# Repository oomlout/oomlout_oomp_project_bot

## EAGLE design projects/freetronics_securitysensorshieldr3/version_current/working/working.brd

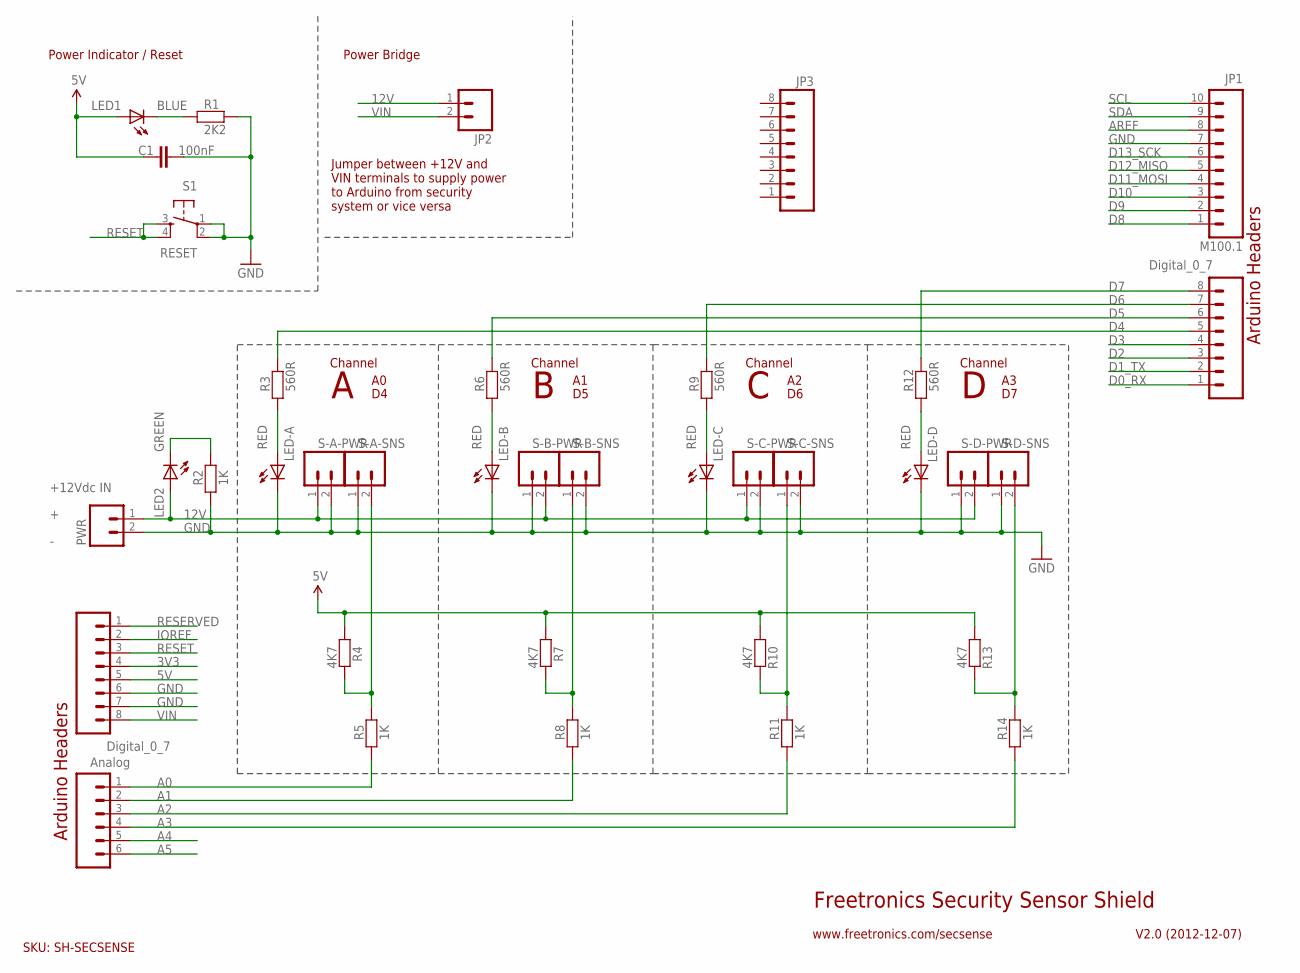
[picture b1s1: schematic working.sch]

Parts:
C1: 100nF; FREETRONICS_CAP-PTH-SMALL
J1, J3: Digital_0_7; 1X08
J2: Analog; 1X06
JP1: M100.1; 1X10
JP2: M02PTH; 1X02
JP3: M08; TERMINALBLOCK_3.5MM_8
LED1: BLUE; LED3MM
LED2: GREEN; LED3MM
LED-A: RED; LED3MM
LED-B: RED; LED3MM
LED-C: RED; LED3MM
LED-D: RED; LED3MM
PWR: M025MM; SCREWTERMINAL-5MM-2
R1: 2K2; FREETRONICS_AXIAL-0.4
R2, R5, R8, R11, R14: 1K; FREETRONICS_AXIAL-0.4
R3, R6, R9, R12: 560R; FREETRONICS_AXIAL-0.4
R4, R7, R10, R13: 4K7; FREETRONICS_AXIAL-0.4
S1: RESET; FREETRONICS_TACTILE-PTH
S-A-PWR: M025MM; SCREWTERMINAL-5MM-2
S-A-SNS: M025MM; SCREWTERMINAL-5MM-2
S-B-PWR: M025MM; SCREWTERMINAL-5MM-2
S-B-SNS: M025MM; SCREWTERMINAL-5MM-2
S-C-PWR: M025MM; SCREWTERMINAL-5MM-2
S-C-SNS: M025MM; SCREWTERMINAL-5MM-2
S-D-PWR: M025MM; SCREWTERMINAL-5MM-2
S-D-SNS: M025MM; SCREWTERMINAL-5MM-2

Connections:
3V3: J3.4
5V: C1.1, J3.5, LED1.A, R4.P$1 (1), R7.P$1 (1), R10.P$1 (1), R13.P$1 (1)
12V: JP2.1, LED2.A, PWR.1, S-A-PWR.1, S-B-PWR.2, S-C-PWR.1, S-D-PWR.2
A0: J2.1, R5.P$1 (1)
A1: J2.2, R8.P$1 (1)
A2: J2.3, R11.P$1 (1)
A3: J2.4, R14.P$1 (1)
A4: J2.5
A5: J2.6
AREF: JP1.8
D0_RX: J1.1
D1_TX: J1.2
D2: J1.3
D3: J1.4
D4: J1.5, R3.P$2 (2)
D5: J1.6, R6.P$2 (2)
D6: J1.7, R9.P$2 (2)
D7: J1.8, R12.P$2 (2)
D8: JP1.1
D9: JP1.2
D10: JP1.3
D11_MOSI: JP1.4
D12_MISO: JP1.5
D13_SCK: JP1.6
GND: C1.2, J3.6, J3.7, JP1.7, LED-A.K (C), LED-B.K (C), LED-C.K (C), LED-D.K (C), PWR.2, R1.P$2 (2), R2.P$1 (1), S1.1, S1.2, S-A-PWR.2, S-A-SNS.1, S-B-PWR.1, S-B-SNS.2, S-C-PWR.2, S-C-SNS.2, S-D-PWR.1, S-D-SNS.1
IOREF: J3.2
unnamed: LED2.K (C), R2.P$2 (2)
unnamed: R7.P$2 (2), R8.P$2 (2), S-B-SNS.1
unnamed: LED1.K (C), R1.P$1 (1)
unnamed: R10.P$2 (2), R11.P$2 (2), S-C-SNS.1
unnamed: LED-D.A, R12.P$1 (1)
unnamed: LED-C.A, R9.P$1 (1)
unnamed: LED-B.A, R6.P$1 (1)
unnamed: LED-A.A, R3.P$1 (1)
unnamed: R13.P$2 (2), R14.P$2 (2), S-D-SNS.2
unnamed: R4.P$2 (2), R5.P$2 (2), S-A-SNS.2
RESERVED: J3.1
RESET: J3.3, S1.3, S1.4
SCL: JP1.10
SDA: JP1.9
VIN: J3.8, JP2.2

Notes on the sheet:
Freetronics Security Sensor Shield
V2.0 (2012-12-07)
SKU: SH-SECSENSE
Power Indicator / Reset
Arduino Headers
www.freetronics.com/secsense
Channel
Power Bridge
Jumper between +12V and VIN terminals to supply power to Arduino from security system or vice versa
+12Vdc IN

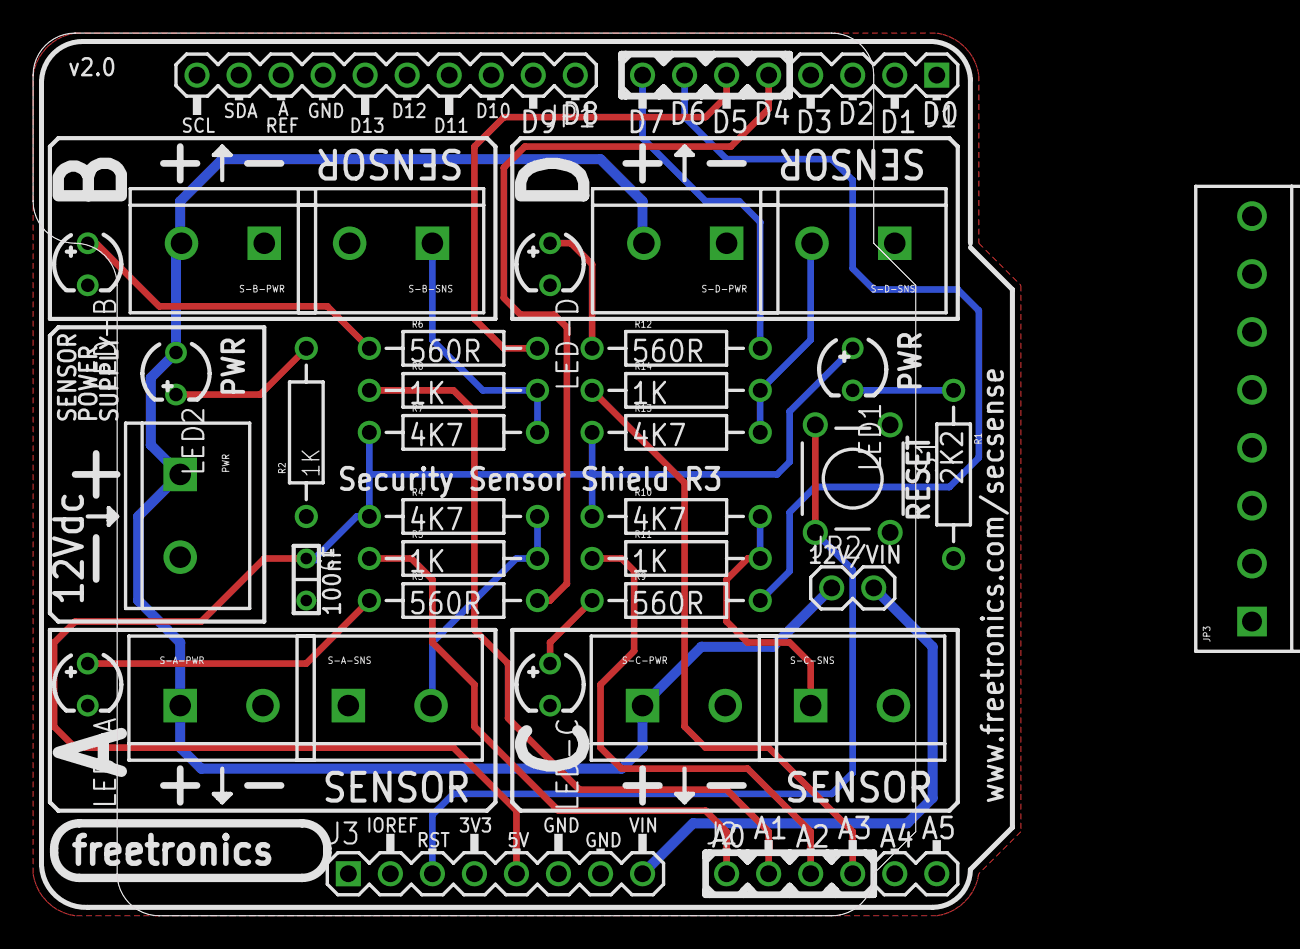
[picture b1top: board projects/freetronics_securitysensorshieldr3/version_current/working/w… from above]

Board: 2 copper layers, 53.3 x 53.3 mm, 37 parts (0 on the bottom side), 23 nets.

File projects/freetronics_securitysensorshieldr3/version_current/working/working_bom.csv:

"Id";"Designator";"Footprint";"Quantity";"Designation";"Supplier and ref";
1;"S-A-SNS0,S-D-PWR0,PWR0,S-B-SNS0,S-D-SNS0,S-C-SNS0,S-A-PWR0,S-C-PWR0,S-B-PWR0";"SCREWTERMINAL-5MM-2";9;"";;;
2;"R9,R3,R6,R12";"FREETRONICS_AXIAL-0.4";4;"560R";;;
3;"R14,R11,R5,R2,R8";"FREETRONICS_AXIAL-0.4";5;"1K";;;
4;"S1";"FREETRONICS_TACTILE-PTH";1;"RESET";;;
5;"LED-B0,LED-C0,LED-A0,LED-D0";"LED3MM";4;"RED";;;
6;"J1,J3";"1X08";2;"Digital_0_7";;;
7;"J2";"1X06";1;"Analog";;;
8;"R13,R7,R4,R10";"FREETRONICS_AXIAL-0.4";4;"4K7";;;
9;"LED1";"LED3MM";1;"BLUE";;;
10;"JP3";"TERMINALBLOCK_3.5MM_8";1;"";;;
11;"R1";"FREETRONICS_AXIAL-0.4";1;"2K2";;;
12;"JP1";"1X10";1;"M100.1";;;
13;"LED2";"LED3MM";1;"GREEN";;;
14;"C1";"FREETRONICS_CAP-PTH-SMALL";1;"100nF";;;
15;"JP2";"1X02";1;"";;;

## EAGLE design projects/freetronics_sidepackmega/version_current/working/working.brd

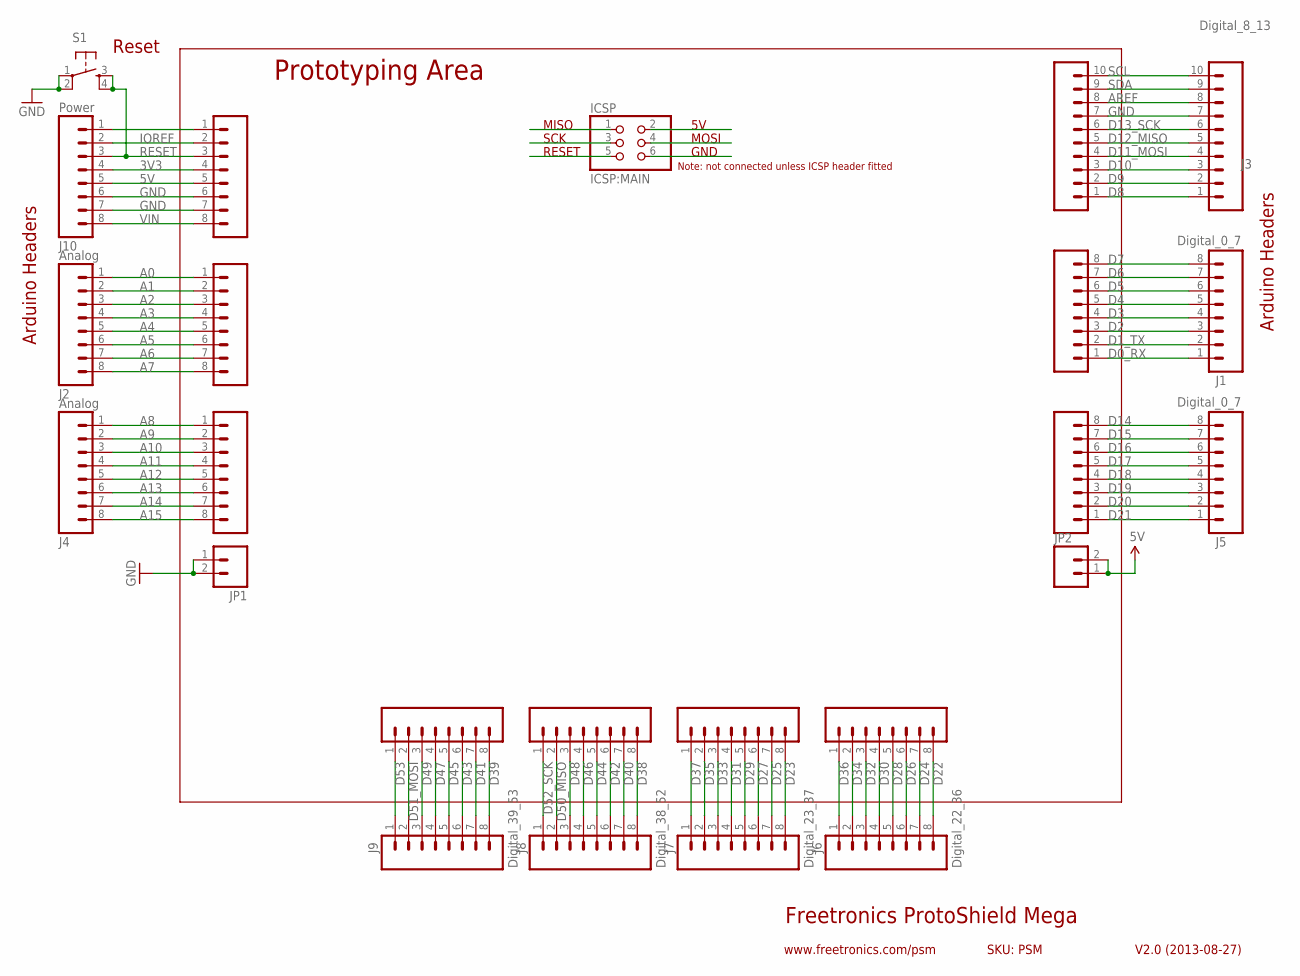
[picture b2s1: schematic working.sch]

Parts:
ICSP: ICSP:MAIN; 2X03
J1, J5: Digital_0_7; 1X08
J2, J4: Analog; 1X08
J3: Digital_8_13; 1X10
J6: Digital_22_36; 1X08
J7: Digital_23_37; 1X08
J8: Digital_38_52; 1X08
J9: Digital_39_53; 1X08
J10: Power; 1X08
JP1, JP2: M02PTH; 1X02
S1: TAC_SWITCHPTH; TACTILE-PTH
SL1, SL5, SL6, SL7, SL8, SL9: Digital_0_7; 1X08
SL2, SL4: Analog; 1X08
SL3: Digital_8_13; 1X10
SLP: Power; 1X08

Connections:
3V3: J10.4, SLP.4
5V: J10.5, JP2.1, JP2.2, SLP.5
A0: J2.1, SL2.1
A1: J2.2, SL2.2
A2: J2.3, SL2.3
A3: J2.4, SL2.4
A4: J2.5, SL2.5
A5: J2.6, SL2.6
A6: J2.7, SL2.7
A7: J2.8, SL2.8
A8: J4.1, SL4.1
A9: J4.2, SL4.2
A10: J4.3, SL4.3
A11: J4.4, SL4.4
A12: J4.5, SL4.5
A13: J4.6, SL4.6
A14: J4.7, SL4.7
A15: J4.8, SL4.8
AREF: J3.8, SL3.8
D0_RX: J1.1, SL1.1
D1_TX: J1.2, SL1.2
D2: J1.3, SL1.3
D3: J1.4, SL1.4
D4: J1.5, SL1.5
D5: J1.6, SL1.6
D6: J1.7, SL1.7
D7: J1.8, SL1.8
D8: J3.1, SL3.1
D9: J3.2, SL3.2
D10: J3.3, SL3.3
D11_MOSI: J3.4, SL3.4
D12_MISO: J3.5, SL3.5
D13_SCK: J3.6, SL3.6
D14: J5.8, SL5.8
D15: J5.7, SL5.7
D16: J5.6, SL5.6
D17: J5.5, SL5.5
D18: J5.4, SL5.4
D19: J5.3, SL5.3
D20: J5.2, SL5.2
D21: J5.1, SL5.1
D22: J6.8, SL6.8
D23: J7.8, SL7.8
D24: J6.7, SL6.7
D25: J7.7, SL7.7
D26: J6.6, SL6.6
D27: J7.6, SL7.6
D28: J6.5, SL6.5
D29: J7.5, SL7.5
D30: J6.4, SL6.4
D31: J7.4, SL7.4
D32: J6.3, SL6.3
D33: J7.3, SL7.3
D34: J6.2, SL6.2
D35: J7.2, SL7.2
D36: J6.1, SL6.1
D37: J7.1, SL7.1
D38: J8.8, SL8.8
D39: J9.8, SL9.8
D40: J8.7, SL8.7
D41: J9.7, SL9.7
D42: J8.6, SL8.6
D43: J9.6, SL9.6
D44: J8.5, SL8.5
D45: J9.5, SL9.5
D46: J8.4, SL8.4
D47: J9.4, SL9.4
D48: J8.3, SL8.3
D49: J9.3, SL9.3
D50_MISO: J8.2, SL8.2
D51_MOSI: J9.2, SL9.2
D52_SCK: J8.1, SL8.1
D53: J9.1, SL9.1
GND: J3.7, J10.6, J10.7, JP1.1, JP1.2, S1.1, S1.2, SL3.7, SLP.6, SLP.7
IOREF: J10.2, SLP.2
unnamed: J10.1, SLP.1
RESET: J10.3, S1.3, S1.4, SLP.3
SCL: J3.10, SL3.10
SDA: J3.9, SL3.9
VIN: J10.8, SLP.8

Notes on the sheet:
Freetronics ProtoShield Mega
V2.0 (2013-08-27)
www.freetronics.com/psm
SKU: PSM
Prototyping Area
Arduino Headers
Reset
GND
MISO
RESET
SCK
MOSI
Note: not connected unless ICSP header fitted

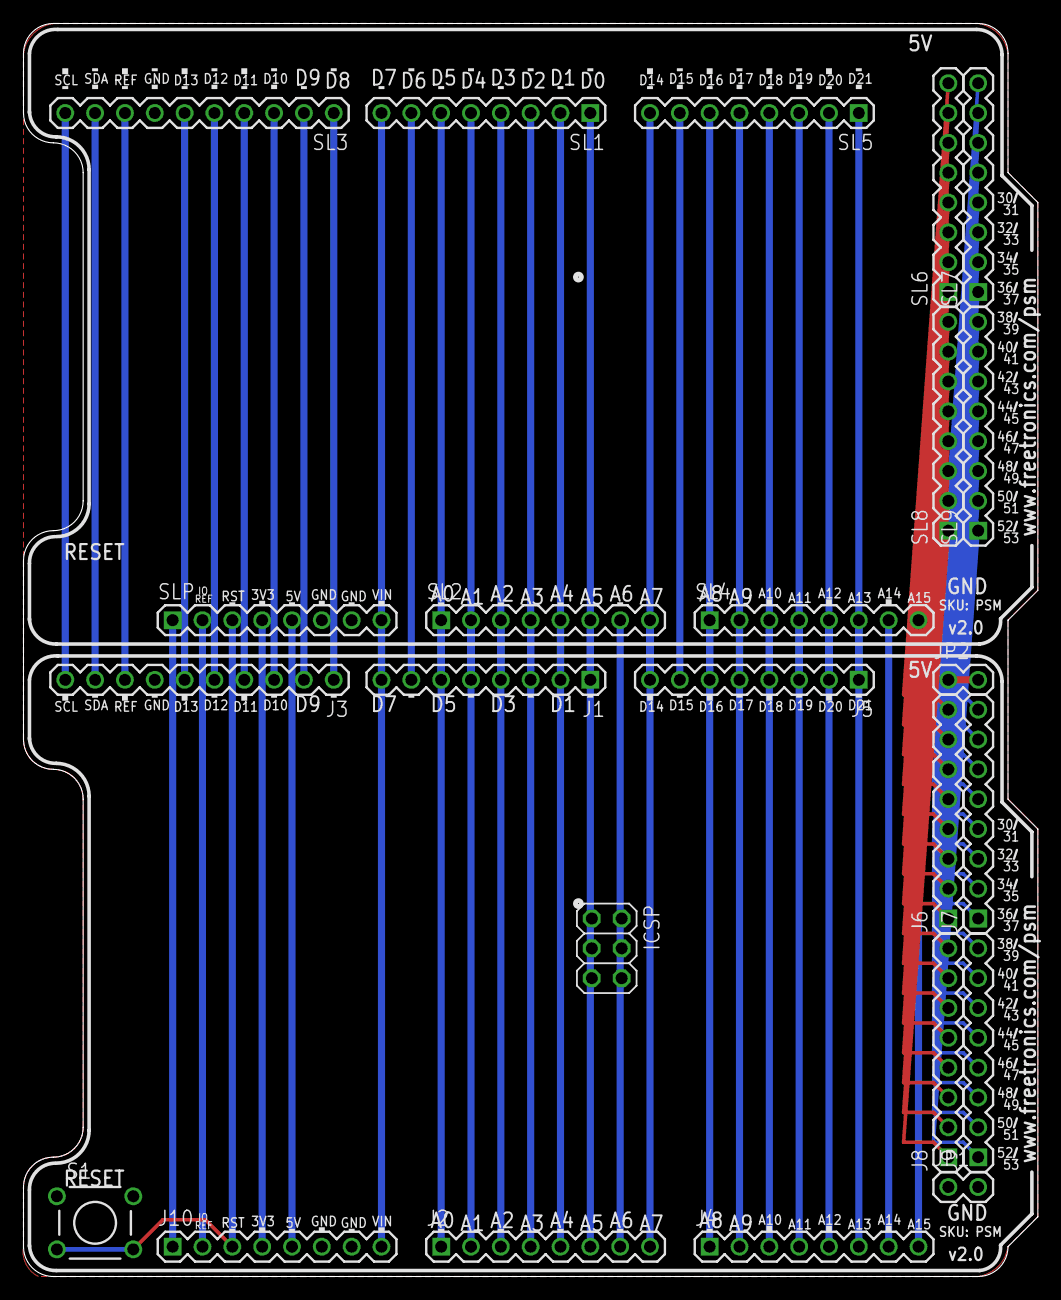
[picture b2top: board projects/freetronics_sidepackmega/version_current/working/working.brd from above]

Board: 2 copper layers, 86.4 x 106.7 mm, 24 parts (0 on the bottom side), 80 nets.

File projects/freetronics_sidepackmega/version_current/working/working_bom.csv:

"Id";"Designator";"Footprint";"Quantity";"Designation";"Supplier and ref";
1;"J1,SL1,J5,SL6,SL9,SL8,SL7,SL5";"1X08";8;"Digital_0_7";;;
2;"J9";"1X08";1;"Digital_39_53";;;
3;"S1";"TACTILE-PTH";1;"";;;
4;"J8";"1X08";1;"Digital_38_52";;;
5;"J7";"1X08";1;"Digital_23_37";;;
6;"ICSP0";"2X03";1;"ICSP:MAIN";;;
7;"JP2,JP1";"1X02";2;"";;;
8;"J6";"1X08";1;"Digital_22_36";;;
9;"SL4,SL2,J2,J4";"1X08";4;"Analog";;;
10;"SLP0,J10";"1X08";2;"Power";;;
11;"SL3,J3";"1X10";2;"Digital_8_13";;;

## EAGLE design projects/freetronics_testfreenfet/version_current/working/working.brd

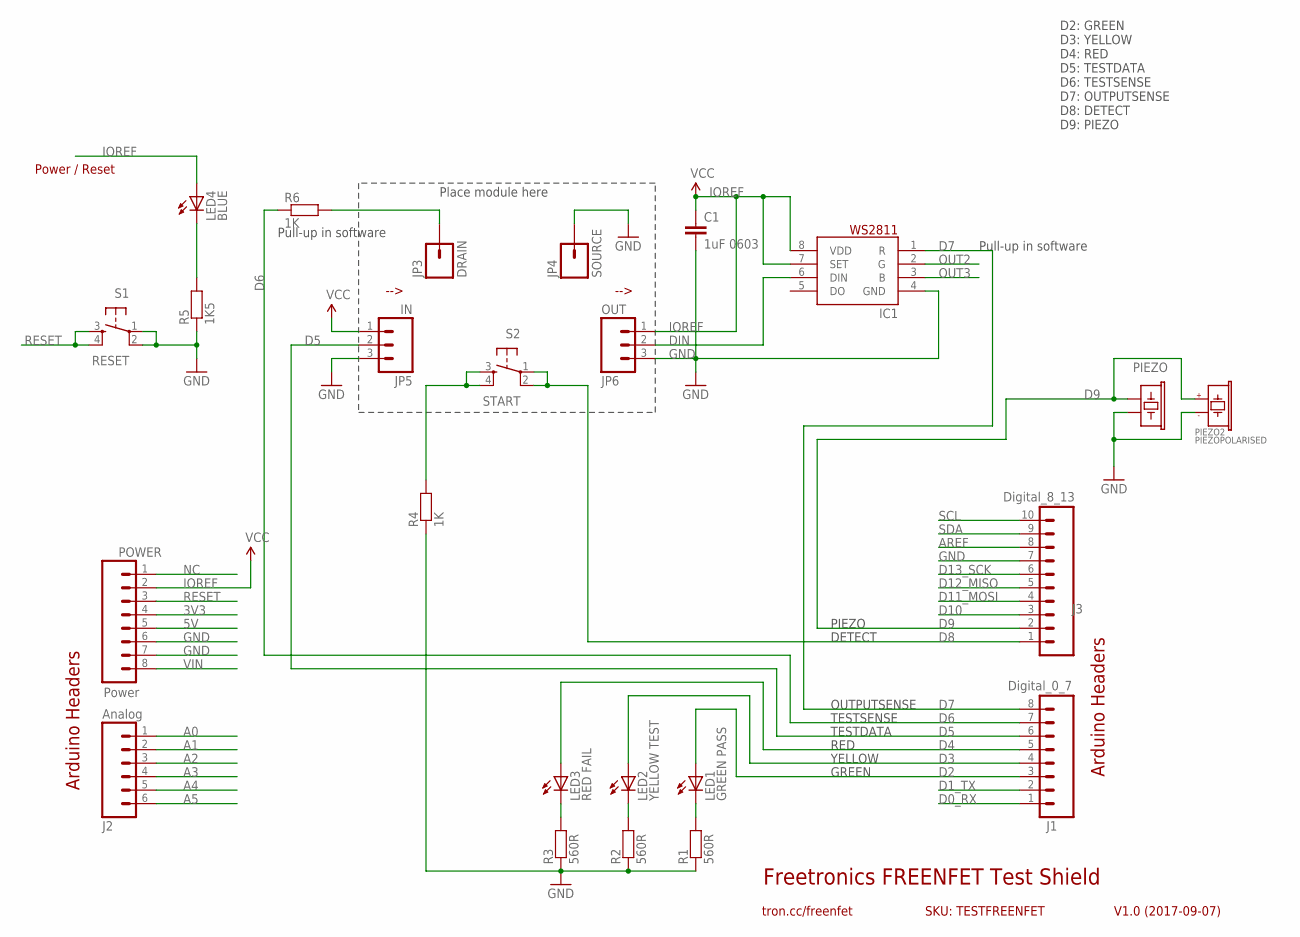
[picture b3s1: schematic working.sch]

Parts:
C1: 1uF 0603; 0603
IC1: WS2811-SOP8; SO08-SKINNYPADS
J1: Digital_0_7; 1X08
J2: Analog; 1X06
J3: Digital_8_13; 1X10
JP3: DRAIN; 1X01_2_1_MM
JP4: SOURCE; 1X01_2_1_MM
JP5: IN; 1X03
JP6: OUT; 1X03
LED1: GREEN PASS; LED-0603
LED2: YELLOW TEST; LED-0603
LED3: RED FAIL; LED-0603
LED4: BLUE; LED-0603
PIEZO: BUZZERSMD12X12; BUZZER-12X12-SMT
PIEZO2: PIEZOPOLARISED; PIEZO12MMWIDEPOLARISED
POWER: Power; 1X08
R1, R2, R3: 560R; 0603
R4, R6: 1K; 0603
R5: 1K5; 0603
S1: RESET; TACTILE-PTH
S2: START; TACTILE-PTH

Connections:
3V3: POWER.4
5V: POWER.5
A0: J2.1
A1: J2.2
A2: J2.3
A3: J2.4
A4: J2.5
A5: J2.6
AREF: J3.8
D0_RX: J1.1
D1_TX: J1.2
D2: J1.3, LED1.A
D3: J1.4, LED2.A
D4: J1.5, LED3.A
D5: J1.6, JP5.2
D6: J1.7, R6.1
D7: IC1.1 (R), J1.8
D8: J3.1, S2.1, S2.2
D9: J3.2, PIEZO.2, PIEZO2.1 (+)
D10: J3.3
D11_MOSI: J3.4
D12_MISO: J3.5
D13_SCK: J3.6
DIN: IC1.6 (DIN), JP6.2
GND: C1.2, IC1.4 (GND), J3.7, JP4.1, JP5.3, JP6.3, PIEZO.1, PIEZO2.2 (-), POWER.6, POWER.7, R1.1, R2.1, R3.1, R4.1, R5.1, S1.1, S1.2
IOREF: C1.1, IC1.7 (SET), IC1.8 (VDD), JP5.1, JP6.1, LED4.A, POWER.2
unnamed: LED1.C, R1.2
unnamed: LED2.C, R2.2
unnamed: LED3.C, R3.2
unnamed: LED4.C, R5.2
unnamed: JP3.1, R6.2
unnamed: R4.2, S2.3, S2.4
NC: POWER.1
OUT2: IC1.2 (G)
OUT3: IC1.3 (B)
RESET: POWER.3, S1.3, S1.4
SCL: J3.10
SDA: J3.9
VIN: POWER.8

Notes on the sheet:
Freetronics FREENFET Test Shield
V1.0 (2017-09-07)
tron.cc/freenfet
SKU: TESTFREENFET
Arduino Headers
Power / Reset
-->
Pull-up in software
Place module here
D2: GREEN D3: YELLOW D4: RED D5: TESTDATA D6: TESTSENSE D7: OUTPUTSENSE D8: DETECT D9: PIEZO
TESTDATA
GREEN
YELLOW
RED
TESTSENSE
OUTPUTSENSE
DETECT
PIEZO

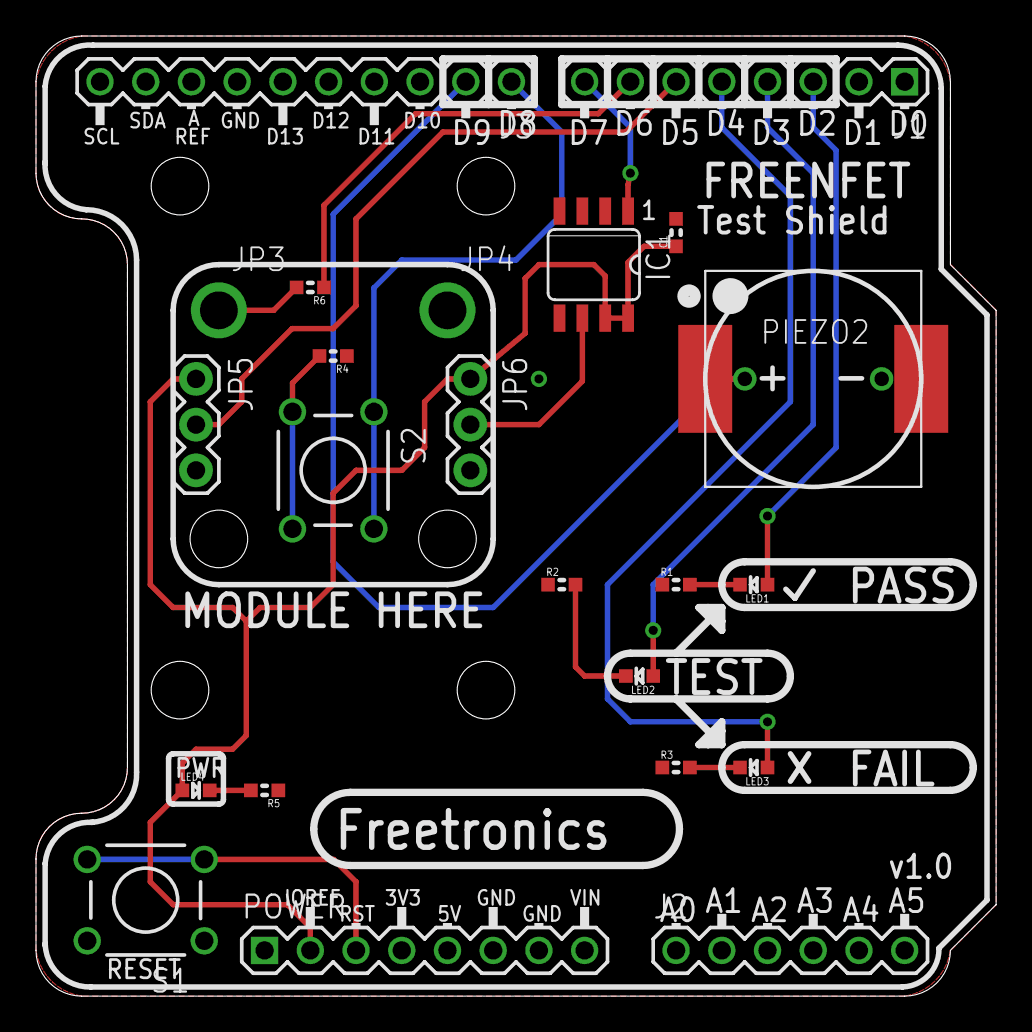
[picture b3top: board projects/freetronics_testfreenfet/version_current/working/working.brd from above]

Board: 2 copper layers, 53.3 x 53.3 mm, 24 parts (0 on the bottom side), 18 nets.

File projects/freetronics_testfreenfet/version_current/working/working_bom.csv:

"Id";"Designator";"Footprint";"Quantity";"Designation";"Supplier and ref";
1;"S2";"TACTILE-PTH";1;"START";;;
2;"JP5";"1X03";1;"IN";;;
3;"C1";"0603";1;"1uF 0603";;;
4;"PIEZO2";"PIEZO12MMWIDEPOLARISED";1;"PIEZOPOLARISED";;;
5;"IC1";"SO08-SKINNYPADS";1;"WS2811-SOP8";;;
6;"LED2";"LED-0603";1;"YELLOW TEST";;;
7;"JP4";"1X01_2_1_MM";1;"SOURCE";;;
8;"R2,R1,R3";"0603";3;"560R";;;
9;"@HOLE2,@HOLE3,@HOLE5,@HOLE1,@HOLE0,@HOLE4";"";6;"";;;
10;"R5";"0603";1;"1K5";;;
11;"POWER0";"1X08";1;"Power";;;
12;"LED3";"LED-0603";1;"RED FAIL";;;
13;"LED4";"LED-0603";1;"BLUE";;;
14;"J2";"1X06";1;"Analog";;;
15;"J1";"1X08";1;"Digital_0_7";;;
16;"J3";"1X10";1;"Digital_8_13";;;
17;"JP6";"1X03";1;"OUT";;;
18;"S1";"TACTILE-PTH";1;"RESET";;;
19;"LED1";"LED-0603";1;"GREEN PASS";;;
20;"R6,R4";"0603";2;"1K";;;
21;"PIEZO0";"BUZZER-12X12-SMT";1;"BUZZERSMD12X12";;;
22;"JP3";"1X01_2_1_MM";1;"DRAIN";;;

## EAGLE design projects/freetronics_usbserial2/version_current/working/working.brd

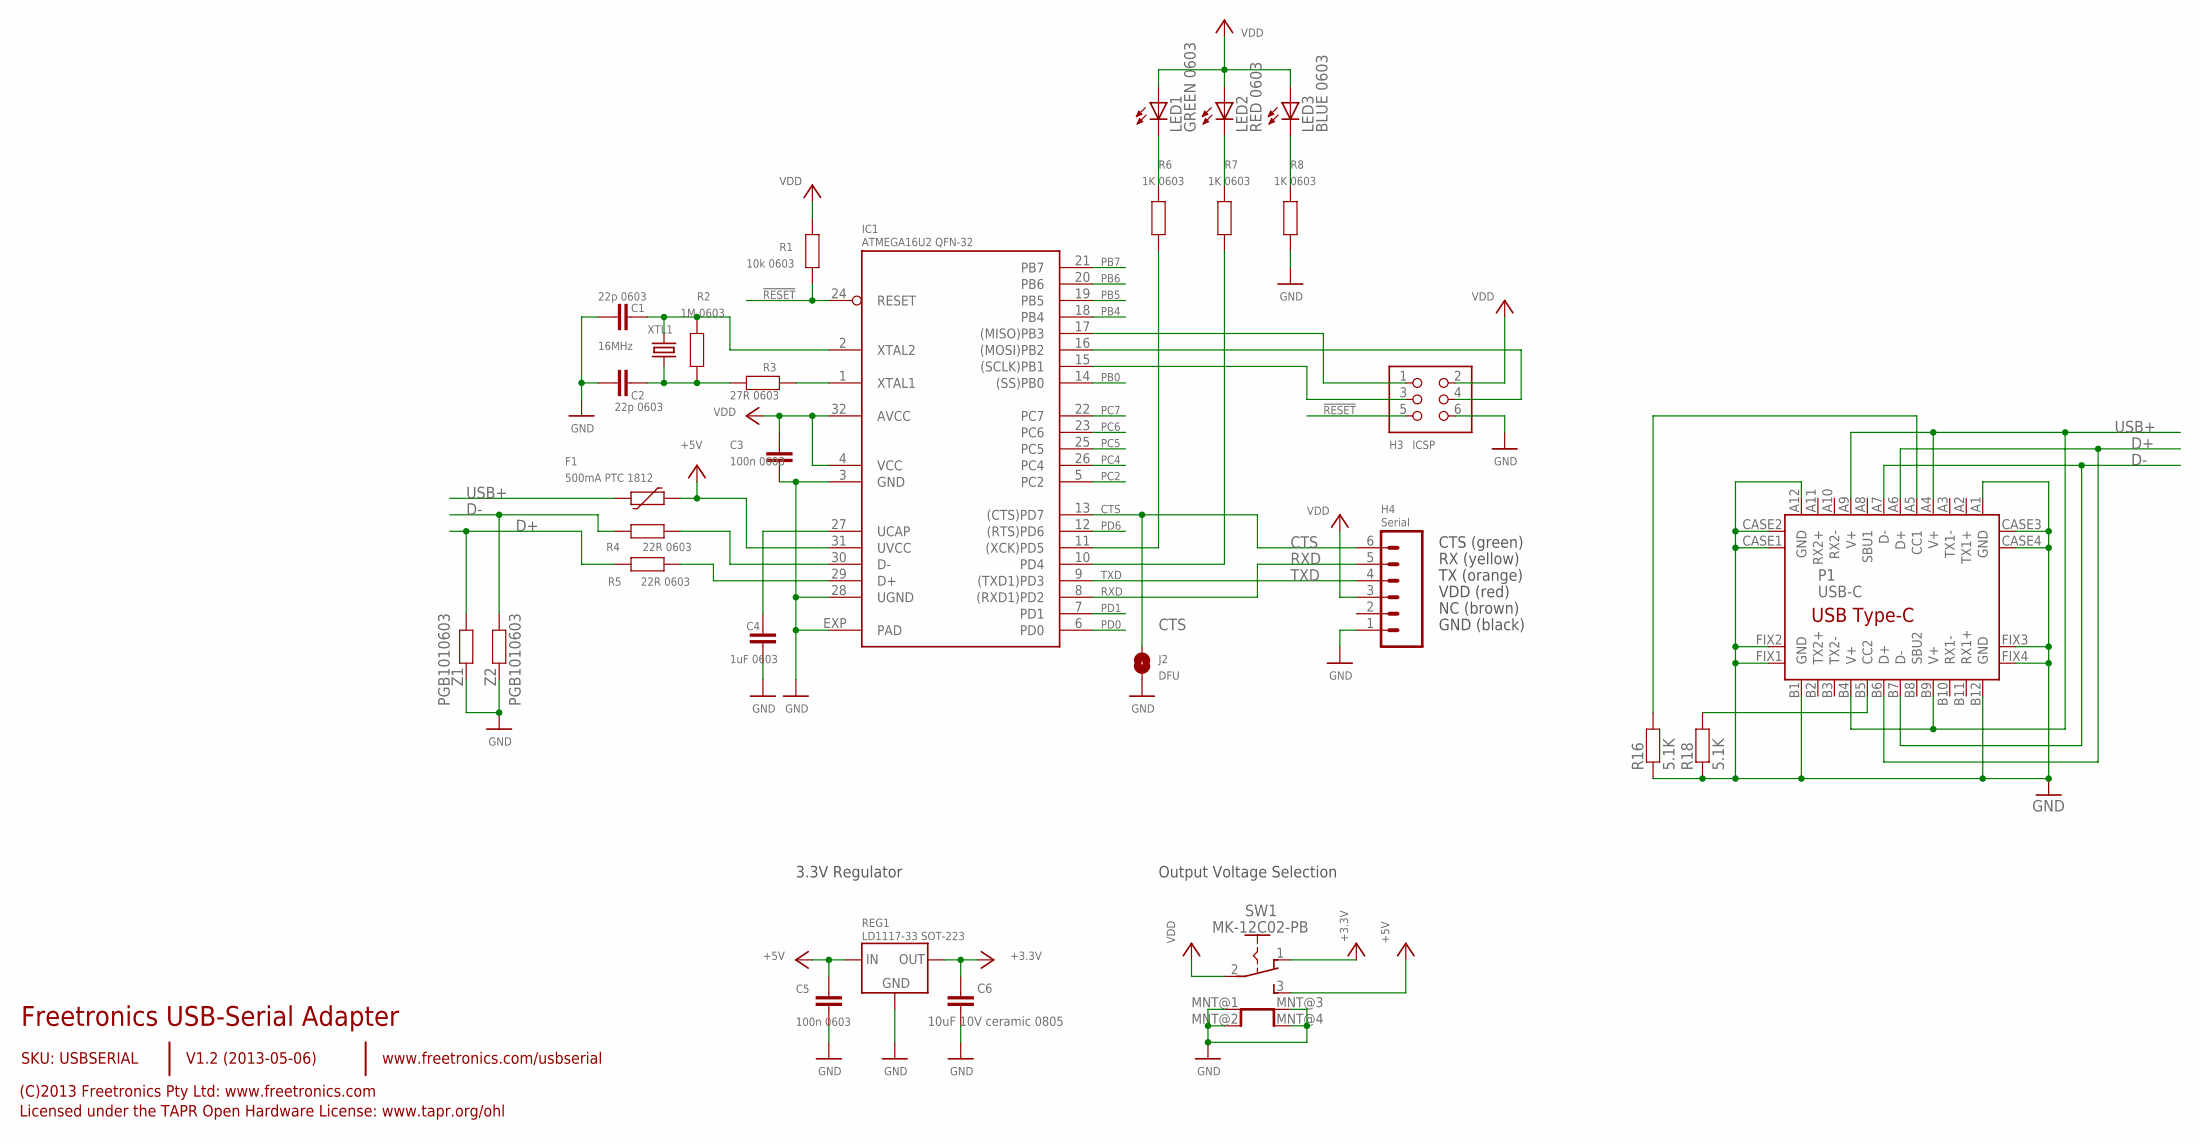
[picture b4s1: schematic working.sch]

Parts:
C1, C2: 22p 0603; 0603
C3, C5: 100n 0603; 0603
C4: 1uF 0603; 0603
C6: 10uF 10V ceramic 0805; C0805
F1: 500mA PTC 1812; 1812
H3: ICSP; HEADER_2X3
H4: Serial; 1X06
IC1: ATMEGA16U2 QFN-32; ATMEL_QFN32
J2: DFU; SJ
LED1: GREEN 0603; LED-0603
LED2: RED 0603; LED-0603
LED3: BLUE 0603; LED-0603
P1: USB-C; USB-C-U52A
R1: 10k 0603; 0603
R2: 1M 0603; 0603
R3: 27R 0603; 0603
R4, R5: 22R 0603; 0603
R6, R7, R8: 1K 0603; 0603
R16, R18: 5.1K; 0603
REG1: LD1117-33 SOT-223; SOT-223
SW1: MK-12C02-PB; MK-12C02
XTL1: 16MHz; HC49U-V
Z1, Z2: PGB1010603; 0603

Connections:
!RESET: H3.5, IC1.24 (RESET), R1.1
+3V3: C6.1, REG1.2 (OUT), REG1.4 (OUT), SW1.1 (A)
+5V: C5.1, F1.2, IC1.31 (UVCC), REG1.3 (IN), SW1.3 (B)
CTS: H4.6, IC1.13 ((CTS)PD7), J2.2
D+: P1.A6 (D+), P1.B6 (D+), R5.2, Z1.1
D-: P1.A7 (D-), P1.B7 (D-), R4.2, Z2.1
GND: C1.1, C2.1, C3.2, C4.2, C5.2, C6.2, H3.6, H4.1, IC1.3 (GND), IC1.28 (UGND), IC1.EXP (PAD), J2.1, P1.A1 (GND), P1.A12 (GND), P1.B1 (GND), P1.B12 (GND), P1.CASE1 (GND), P1.CASE2 (GND), P1.CASE3 (GND), P1.CASE4 (GND), P1.FIX1 (GND), P1.FIX2 (GND), P1.FIX3 (GND), P1.FIX4 (GND), R8.1, R16.1, R18.1, REG1.1 (GND), SW1.MNT@1 (MNT), SW1.MNT@2 (MNT), SW1.MNT@3 (MNT), SW1.MNT@4 (MNT), Z1.2, Z2.2
MISO: H3.1, IC1.17 ((MISO)PB3)
MOSI: H3.4, IC1.16 ((MOSI)PB2)
unnamed: IC1.1 (XTAL1), R3.1
unnamed: LED1.C, R6.2
unnamed: P1.A5 (CC1), R16.2
unnamed: P1.B5 (CC2), R18.2
unnamed: LED2.C, R7.2
unnamed: LED3.C, R8.2
unnamed: C1.2, IC1.2 (XTAL2), R2.2, XTL1.2
unnamed: C2.2, R2.1, R3.2, XTL1.1
unnamed: C4.1, IC1.27 (UCAP)
PB0: IC1.14 ((SS)PB0)
PB4: IC1.18 (PB4)
PB5: IC1.19 (PB5)
PB6: IC1.20 (PB6)
PB7: IC1.21 (PB7)
PC2: IC1.5 (PC2)
PC4: IC1.26 (PC4)
PC5: IC1.25 (PC5)
PC6: IC1.23 (PC6)
PC7: IC1.22 (PC7)
PD0: IC1.6 (PD0)
PD1: IC1.7 (PD1)
PD6: IC1.12 ((RTS)PD6)
RD+: IC1.29 (D+), R5.1
RD-: IC1.30 (D-), R4.1
RXD: H4.5, IC1.8 ((RXD1)PD2)
RXLED: IC1.10 (PD4), R7.1
SCK: H3.3, IC1.15 ((SCLK)PB1)
TXD: H4.4, IC1.9 ((TXD1)PD3)
TXLED: IC1.11 ((XCK)PD5), R6.1
USB+: F1.1, P1.A4 (V+), P1.A9 (V+), P1.B4 (V+), P1.B9 (V+)
VDD: C3.1, H3.2, H4.3, IC1.4 (VCC), IC1.32 (AVCC), LED1.A, LED2.A, LED3.A, R1.2, SW1.2 (COM)

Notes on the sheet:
Freetronics USB-Serial Adapter
V1.2 (2013-05-06)
SKU: USBSERIAL
(C)2013 Freetronics Pty Ltd: www.freetronics.com
Licensed under the TAPR Open Hardware License: www.tapr.org/ohl
www.freetronics.com/usbserial
CTS (green)
RX (yellow)
TX (orange)
VDD (red)
NC (brown)
GND (black)
Output Voltage Selection
3.3V Regulator

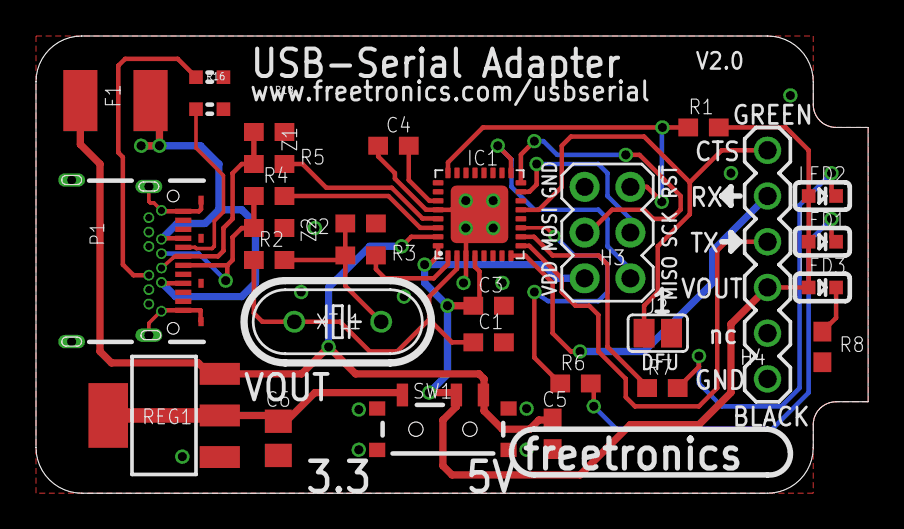
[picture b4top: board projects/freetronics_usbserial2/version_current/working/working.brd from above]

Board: 2 copper layers, 46.2 x 25.4 mm, 30 parts (0 on the bottom side), 27 nets.

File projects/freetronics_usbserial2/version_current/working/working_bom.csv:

"Id";"Designator";"Footprint";"Quantity";"Designation";"Supplier and ref";
1;"Z2,Z1";"0603";2;"PGB1010603";;;
2;"REG1";"SOT-223";1;"LD1117-33 SOT-223";;;
3;"R7,R8,R6";"0603";3;"1K 0603";;;
4;"XTL1";"HC49U-V";1;"16MHz";;;
5;"LED3";"LED-0603";1;"BLUE 0603";;;
6;"R4,R5";"0603";2;"22R 0603";;;
7;"R16,R18";"0603";2;"5.1K";;;
8;"H4";"1X06";1;"Serial";;;
9;"C5,C3";"0603";2;"100n 0603";;;
10;"C4";"0603";1;"1uF 0603";;;
11;"J2";"SJ";1;"DFU";;;
12;"IC1";"ATMEL_QFN32";1;"ATMEGA16U2 QFN-32";;;
13;"LED1";"LED-0603";1;"GREEN 0603";;;
14;"P1";"USB-C-U52A";1;"USB-C";;;
15;"LED2";"LED-0603";1;"RED 0603";;;
16;"SW1";"MK-12C02";1;"MK-12C02-PB";;;
17;"C6";"C0805";1;"10uF 10V ceramic 0805";;;
18;"F1";"1812";1;"500mA PTC 1812";;;
19;"R1";"0603";1;"10k 0603";;;
20;"C1,C2";"0603";2;"22p 0603";;;
21;"R3";"0603";1;"27R 0603";;;
22;"H3";"HEADER_2X3";1;"ICSP";;;
23;"R2";"0603";1;"1M 0603";;;

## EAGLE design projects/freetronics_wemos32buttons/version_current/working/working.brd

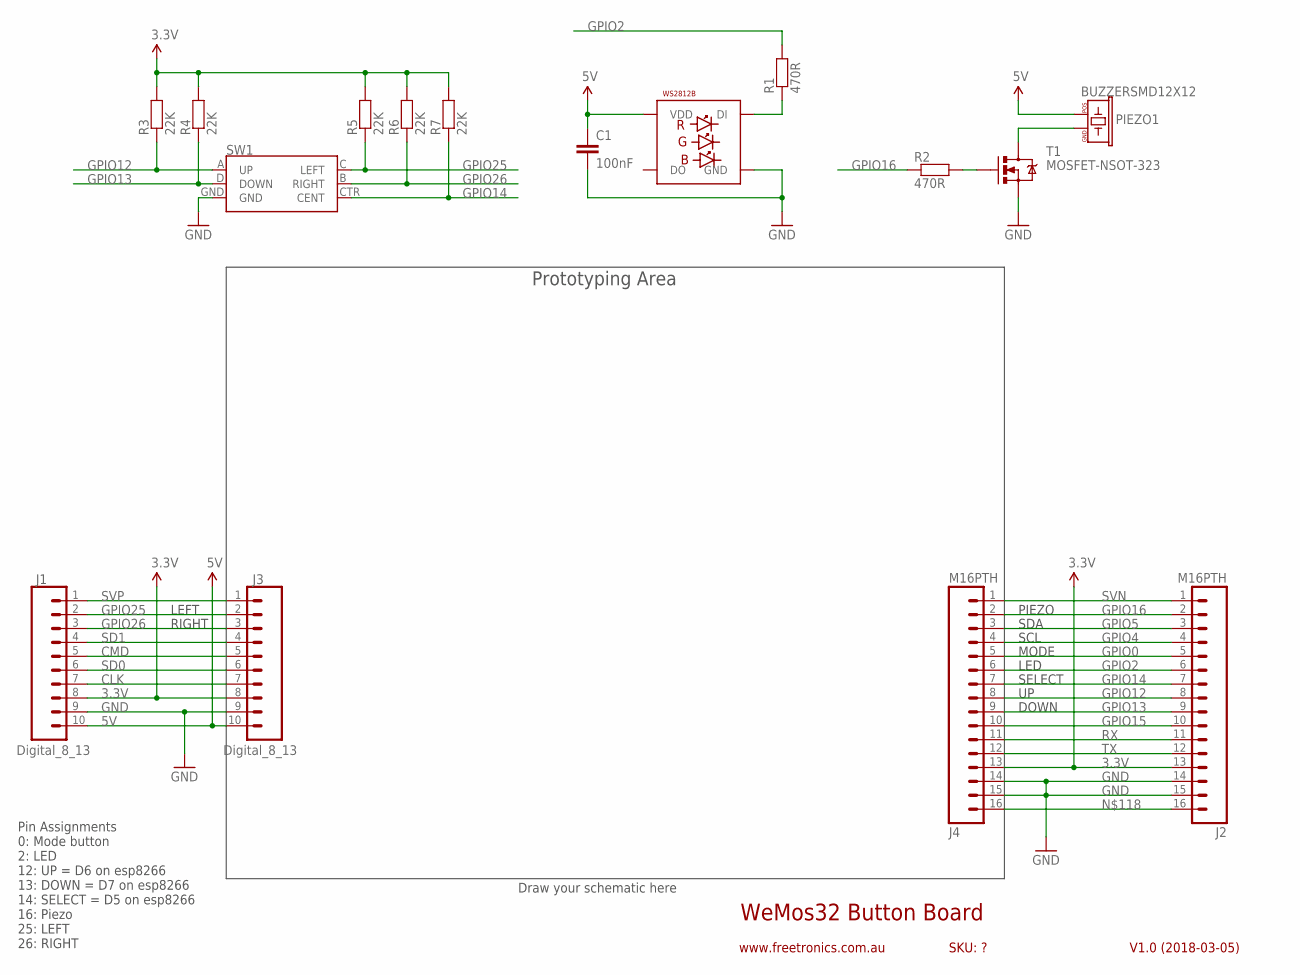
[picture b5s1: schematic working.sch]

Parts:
C1: 100nF; 0603
J1, J3: Digital_8_13; 1X10
J2, J4: M16PTH; 1X16
LED2: WS2812B5050; WS2812B
PIEZO1: BUZZERSMD12X12; BUZZER-12X12-SMT
R1, R2: 470R; 0603
R3, R4, R5, R6, R7: 22K; 0603
SW1: JOYSTICK_MINI
T1: MOSFET-NSOT-323; SOT32-3

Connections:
3.3V: J1.8, J2.13, J3.8, J4.13, R3.2, R4.2, R5.2, R6.2, R7.2
5V: C1.1, J1.10, J3.10, LED2.1-VDD (VDD), PIEZO1.2 (POS)
CLK: J1.7, J3.7
CMD: J1.5, J3.5
GND: C1.2, J1.9, J2.14, J2.15, J3.9, J4.14, J4.15, LED2.3-GND (GND), SW1.GND, T1.2 (S)
GPIO0: J2.5, J4.5
GPIO2: J2.6, J4.6, R1.2
GPIO4: J2.4, J4.4
GPIO5: J2.3, J4.3
GPIO12: J2.8, J4.8, R3.1, SW1.A (UP)
GPIO13: J2.9, J4.9, R4.1, SW1.D (DOWN)
GPIO14: J2.7, J4.7, R7.1, SW1.CTR (CENT)
GPIO15: J2.10, J4.10
GPIO16: J2.2, J4.2, R2.1
GPIO25: J1.2, J3.2, R5.1, SW1.C (LEFT)
GPIO26: J1.3, J3.3, R6.1, SW1.B (RIGHT)
unnamed: PIEZO1.1 (GND), T1.3 (D)
unnamed: R2.2, T1.1 (G)
unnamed: J2.16, J4.16
unnamed: LED2.4-DIN (DI), R1.1
RX: J2.11, J4.11
SD0: J1.6, J3.6
SD1: J1.4, J3.4
SVN: J2.1, J4.1
SVP: J1.1, J3.1
TX: J2.12, J4.12

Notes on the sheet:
WeMos32 Button Board
V1.0 (2018-03-05)
www.freetronics.com.au
SKU: ?
Pin Assignments 0: Mode button 2: LED 12: UP = D6 on esp8266 13: DOWN = D7 on esp8266 14: SELECT = D5 on esp8266 16: Piezo 25: LEFT 26: RIGHT
Draw your schematic here
Prototyping Area
LED
DOWN
SELECT
MODE
SDA
SCL
PIEZO
LEFT
RIGHT

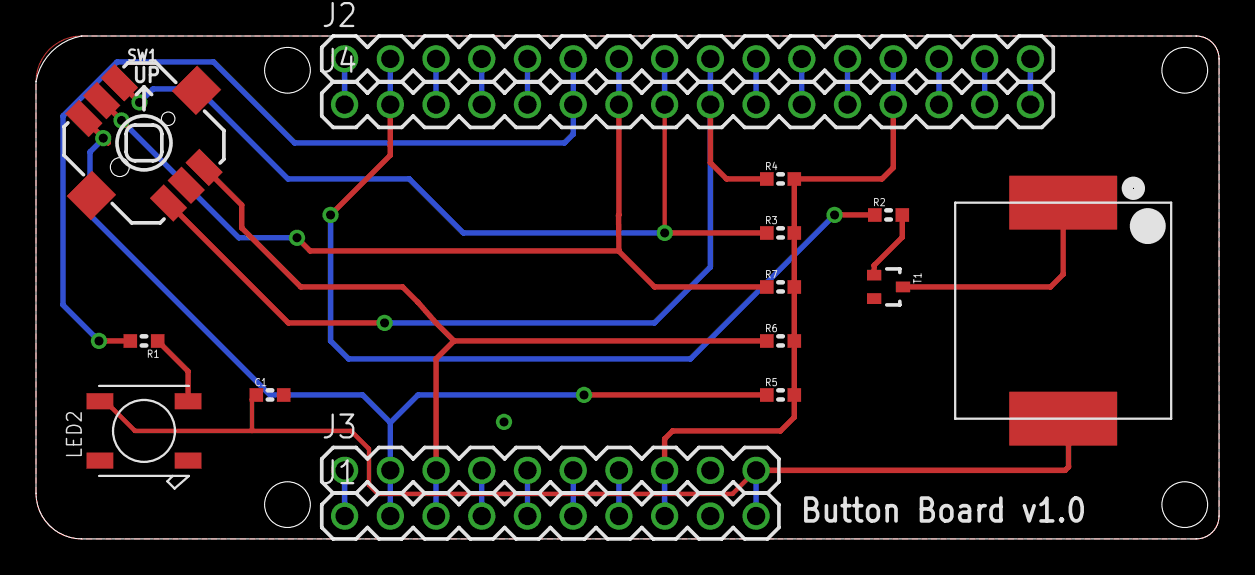
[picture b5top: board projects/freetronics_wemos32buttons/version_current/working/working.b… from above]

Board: 2 copper layers, 65.7 x 27.9 mm, 16 parts (0 on the bottom side), 26 nets.

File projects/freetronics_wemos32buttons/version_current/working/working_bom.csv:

"Id";"Designator";"Footprint";"Quantity";"Designation";"Supplier and ref";
1;"R3,R5,R7,R6,R4";"0603";5;"22K";;;
2;"@HOLE2,@HOLE1,@HOLE3,@HOLE0";"";4;"";;;
3;"PIEZO1";"BUZZER-12X12-SMT";1;"BUZZERSMD12X12";;;
4;"J4,J2";"1X16";2;"M16PTH";;;
5;"J3,J1";"1X10";2;"Digital_8_13";;;
6;"C1";"0603";1;"100nF";;;
7;"LED2";"WS2812B";1;"WS2812B5050";;;
8;"SW1";"JOYSTICK_MINI";1;"";;;
9;"R2,R1";"0603";2;"470R";;;
10;"T1";"SOT32-3";1;"MOSFET-NSOT-323";;;

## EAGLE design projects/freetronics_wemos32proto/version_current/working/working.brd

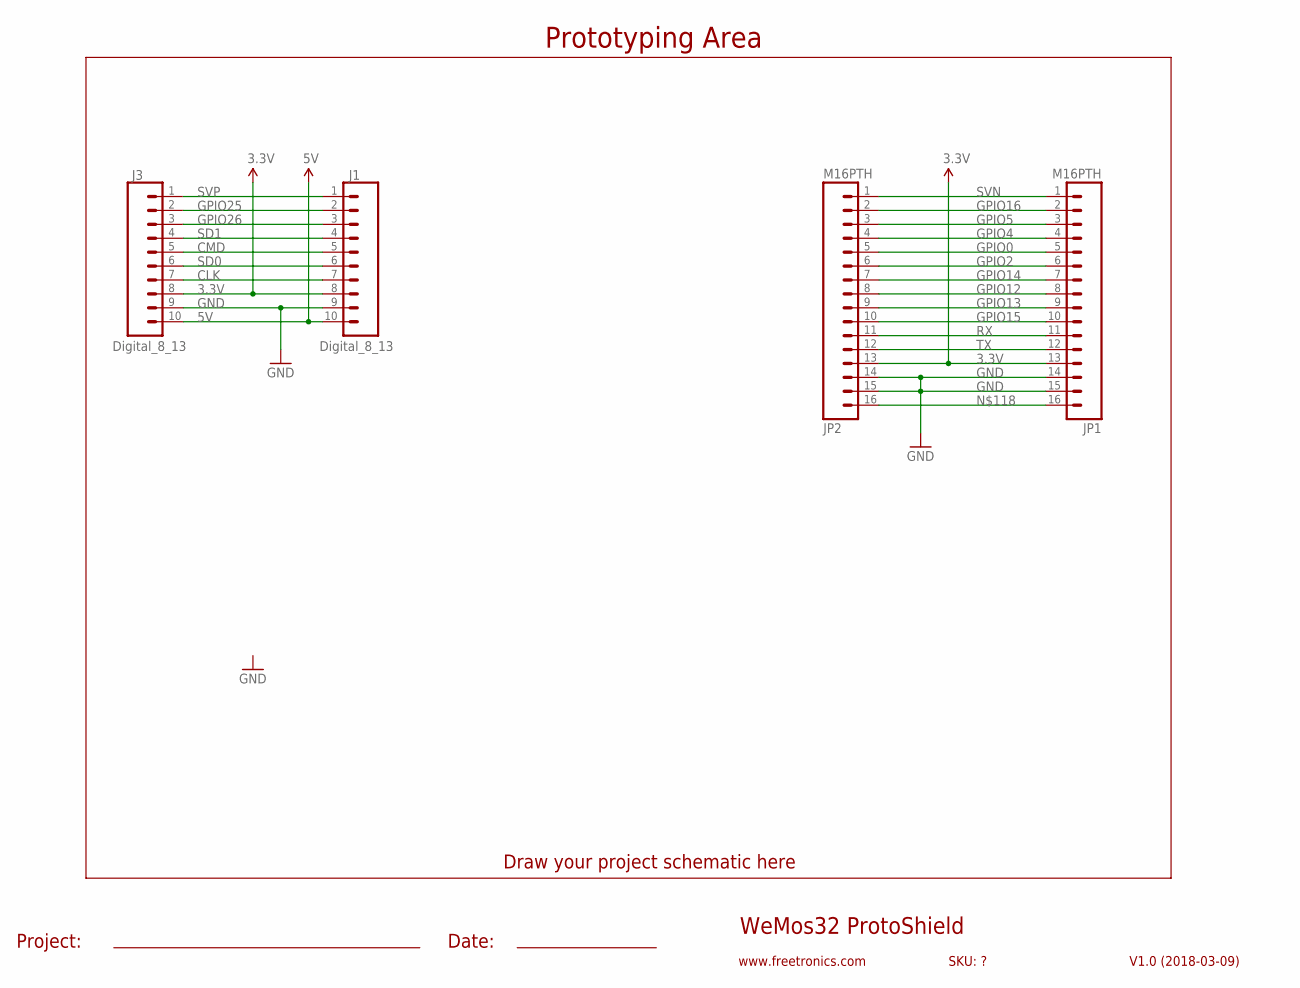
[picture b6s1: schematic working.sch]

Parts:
J1, J3: Digital_8_13; 1X10
JP1, JP2: M16PTH; 1X16

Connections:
3.3V: J1.8, J3.8, JP1.13, JP2.13
5V: J1.10, J3.10
CLK: J1.7, J3.7
CMD: J1.5, J3.5
GND: J1.9, J3.9, JP1.14, JP1.15, JP2.14, JP2.15
GPIO0: JP1.5, JP2.5
GPIO2: JP1.6, JP2.6
GPIO4: JP1.4, JP2.4
GPIO5: JP1.3, JP2.3
GPIO12: JP1.8, JP2.8
GPIO13: JP1.9, JP2.9
GPIO14: JP1.7, JP2.7
GPIO15: JP1.10, JP2.10
GPIO16: JP1.2, JP2.2
GPIO25: J1.2, J3.2
GPIO26: J1.3, J3.3
unnamed: JP1.16, JP2.16
RX: JP1.11, JP2.11
SD0: J1.6, J3.6
SD1: J1.4, J3.4
SVN: JP1.1, JP2.1
SVP: J1.1, J3.1
TX: JP1.12, JP2.12

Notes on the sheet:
WeMos32 ProtoShield
V1.0 (2018-03-09)
www.freetronics.com
SKU: ?
Prototyping Area
Project:
Date:
Draw your project schematic here

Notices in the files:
projects/freetronics_securitysensorshieldr3/version_current/working/working.brd:
(c) 2012 Freetronics Pty Ltd
projects/freetronics_testfreenfet/version_current/working/working.brd:
(c) 2017 Freetronics Pty Ltd
projects/freetronics_wemos32buttons/version_current/working/working.brd:
(C)2018 Freetronics Pty Ltd
All Rights Reserved
parts and their libraries:
freetronics-original: Licensing: CC v3.0 Share-Alike You are welcome to use this library for commercial purposes.
SparkFun-Switches: Licensing: Creative Commons ShareAlike 4.0 International - https://creativecommons.org/licenses/by-sa/4.0
